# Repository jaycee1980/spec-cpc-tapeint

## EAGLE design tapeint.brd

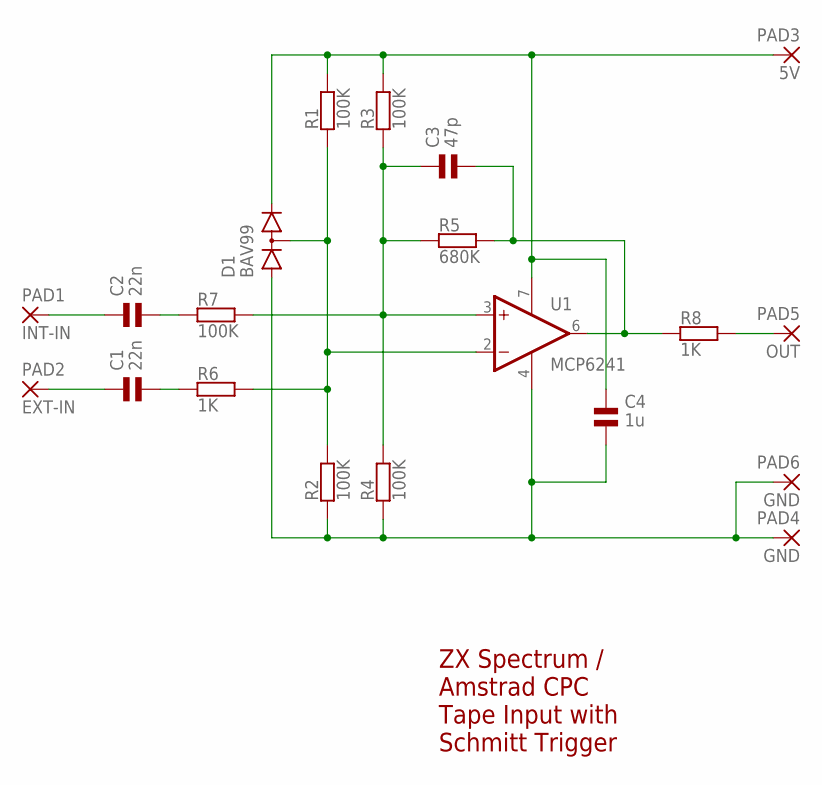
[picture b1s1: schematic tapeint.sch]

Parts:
C1, C2: 22n; 0805
C3: 47p; 0805
C4: 1u; 0805
D1: BAV99; SOT23
PAD1: INT-IN; 2,54/1,0
PAD2: EXT-IN; 2,54/1,0
PAD3: 5V; 2,54/1,0
PAD4, PAD6: GND; 2,54/1,0
PAD5: OUT; 2,54/1,0
R1, R2, R3, R4, R7: 100K; 0805
R5: 680K; 0805
R6, R8: 1K; 0805
U1: MCP6241; SO08

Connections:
+5V: C4.1, D1.2 (K2), PAD3.1, R1.2, R3.2, U1.7 (V+)
GND: C4.2, D1.1 (A1), PAD4.1, PAD6.1, R2.1, R4.1, U1.4 (V-)
unnamed: PAD5.1, R8.2
unnamed: D1.3 (K1A2), R1.1, R2.2, R6.2, U1.2 (-IN)
unnamed: C3.1, R3.1, R4.2, R5.1, R7.2, U1.3 (+IN)
unnamed: C1.1, PAD2.1
unnamed: C1.2, R6.1
unnamed: C2.1, PAD1.1
unnamed: C2.2, R7.1
OUT: C3.2, R5.2, R8.1, U1.6 (OUT)

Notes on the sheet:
ZX Spectrum / Amstrad CPC Tape Input with Schmitt Trigger

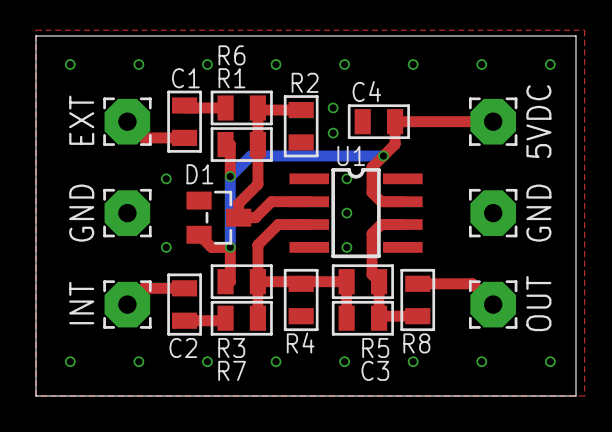
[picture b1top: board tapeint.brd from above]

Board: 2 copper layers, 30.0 x 20.0 mm, 20 parts (0 on the bottom side), 10 nets.

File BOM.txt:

Name			Value		Manufacturer	Description
R1-R4,R7		100K		Generic		Resistor 0805, 1%, 125mW
R5			680K		Generic		Resistor 0805, 1%, 125mW
R6,R8			1K		Generic		Resistor 0805, 1%, 125mW
C1,C2			22n		Generic		Capacitor 0805, 25V, X7R
C3			470n		Generic		Capacitor 0805, 25V, X7R
C4			33p		Generic		Capacitor 0805, 25V, NP0/C0G
U1			MCP6241		Microchip	Opamp, single, SOIC-8 package
(alt)			UA741		Generic

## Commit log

2023-03-21 Doh, missed edits to .gitignore
2023-03-21 Sorted the spacing in the BOM
2023-03-21 Added some pictures for the README
2023-03-21 Added better pictures of the board top
2025-05-19 Updated version with better 0805 footprints, gerbers in a zip file, and BOM/CPL data for jlcpcb
